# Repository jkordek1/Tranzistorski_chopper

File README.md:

# Tranzistorski_chopper

## O projektu
 Tranzistorski chopper korišten za laboratorijske vježbe na elektrotehničkom odjelu TVZ-a.
 
 ## Značajke
 - Ulazni napon do 24V
 - Potenciometar za promjenu širine impulsa visokog stanja PWM-a
 - Ušice za sonde osciloskopa
 - 3 različite frekvencije PWM-a koje se odabiru pomoću kratkospojnika
 
 ## Slike

## Struktura mape
    .
    ├── ...
    ├── 3d modeli               # 3d modeli komponenata
    ├── Images                  # Slike i grafički elementi dodani na pločicu
    ├── KiCad files             # Glavna mapa KiCAD projekta
    │   ├── Board2Pdf           # Montažna shema
    │   ├── bom                 # ibom pomoćna datoteka za montažu komponenata
    │   ├── Dokumentacija       # Električna shema
    │   ├── gerber              # gerber mapa
    │   └── Slike               # 3D render sklopa
    └── ...

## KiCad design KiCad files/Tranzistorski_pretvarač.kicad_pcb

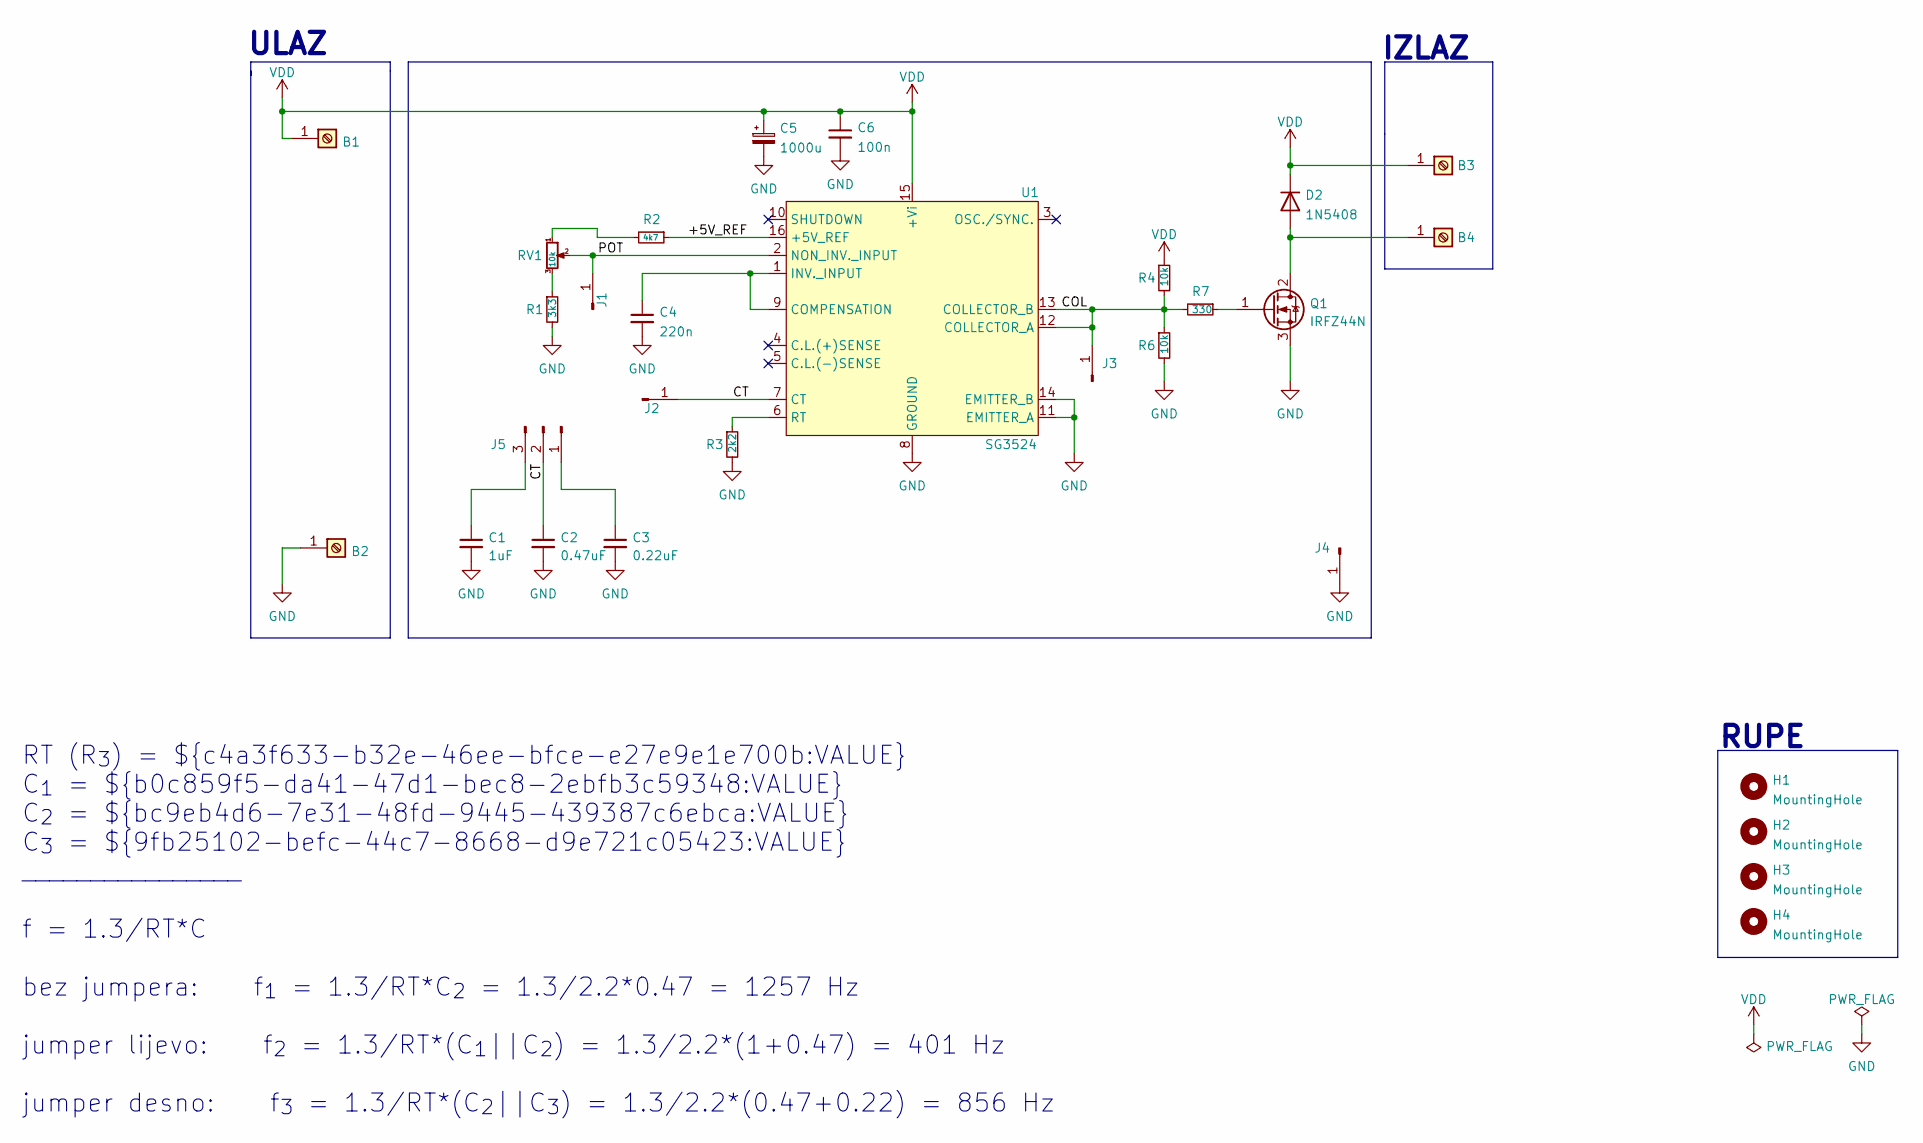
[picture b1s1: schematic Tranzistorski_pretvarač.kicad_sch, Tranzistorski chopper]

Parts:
B1, B3: Screw_Terminal_01x01; DELTRON 4mm banana socket - red
B2, B4: Screw_Terminal_01x01; DELTRON 4mm banana socket - black
C1: 1uF; C_Rect_L7.2mm_W2.5mm_P5.00mm_FKS2_FKP2_MKS2_MKP2
C2: 0.47uF; C_Rect_L7.2mm_W2.5mm_P5.00mm_FKS2_FKP2_MKS2_MKP2
C3: 0.22uF; C_Rect_L7.2mm_W2.5mm_P5.00mm_FKS2_FKP2_MKS2_MKP2
C4: 220n; C_Rect_L7.2mm_W2.5mm_P5.00mm_FKS2_FKP2_MKS2_MKP2
C5: 1000u; CP_Radial_D17.0mm_P7.50mm
C6: 100n; C_Rect_L7.2mm_W2.5mm_P5.00mm_FKS2_FKP2_MKS2_MKP2
D2: 1N5408; D_DO-201AD_P15.24mm_Horizontal
H1, H2, H3, H4: MountingHole; MountingHole_3.2mm_M3
J1, J2, J3, J4: Conn_01x01_Male; oscil
J5: Conn_01x03_Male; PinHeader_1x03_P2.54mm_Vertical
Q1: IRFZ44N; TO-220F-3_Horizontal_TabDown
R1: 3k3; R_Axial_DIN0207_L6.3mm_D2.5mm_P10.16mm_Horizontal
R2: 4k7; R_Axial_DIN0207_L6.3mm_D2.5mm_P10.16mm_Horizontal
R3: 2k2; R_Axial_DIN0207_L6.3mm_D2.5mm_P10.16mm_Horizontal
R4, R6: 10k; R_Axial_DIN0207_L6.3mm_D2.5mm_P10.16mm_Horizontal
R7: 330; R_Axial_DIN0207_L6.3mm_D2.5mm_P10.16mm_Horizontal
RV1: 10k; PTV09A-4225F-B502
U1: SG3524; DIP-16_W7.62mm_Socket_LongPads

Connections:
/+5V_REF: R2.1, U1.16 (+5V_REF)
/COL: J3.1, R4.2, R6.1, R7.2, U1.12 (COLLECTOR_A), U1.13 (COLLECTOR_B)
/CT: C2.1, J2.1, J5.2, U1.7 (CT)
/POT: J1.1, RV1.2, U1.2 (NON_INV._INPUT)
GND: B2.1, C1.2, C2.2, C3.2, C4.2, C5.2, C6.2, J4.1, Q1.3 (S), R1.2, R3.2, R6.2, U1.8 (GROUND), U1.11 (EMITTER_A), U1.14 (EMITTER_B)
unnamed: B4.1, D2.2 (A), Q1.2 (D)
unnamed: C1.1, J5.3
unnamed: C3.1, J5.1
unnamed: C4.1, U1.1 (INV._INPUT), U1.9 (COMPENSATION)
unnamed: Q1.1 (G), R7.1
unnamed: R1.1, RV1.3
unnamed: R2.2, RV1.1
unnamed: R3.1, U1.6 (RT)
VDD: B1.1, B3.1, C5.1, C6.1, D2.1 (K), R4.1, U1.15 (+Vi)

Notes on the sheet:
RUPE
IZLAZ
ULAZ
RT (R_{3}) = ${c4a3f633-b32e-46ee-bfce-e27e9e1e700b:VALUE} C_{1} = ${b0c859f5-da41-47d1-bec8-2ebfb3c59348:VALUE} C_{2} = ${bc9eb4d6-7e31-48fd-9445-439387c6ebca:VALUE} C_{3} = ${9fb25102-befc-44c7-8668-d9e721c05423:VALUE} ________________ f = 1.3/RT*C bez jumpera: f_{1} = 1.3/RT*C_{2} = 1.3/2.2*0.47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

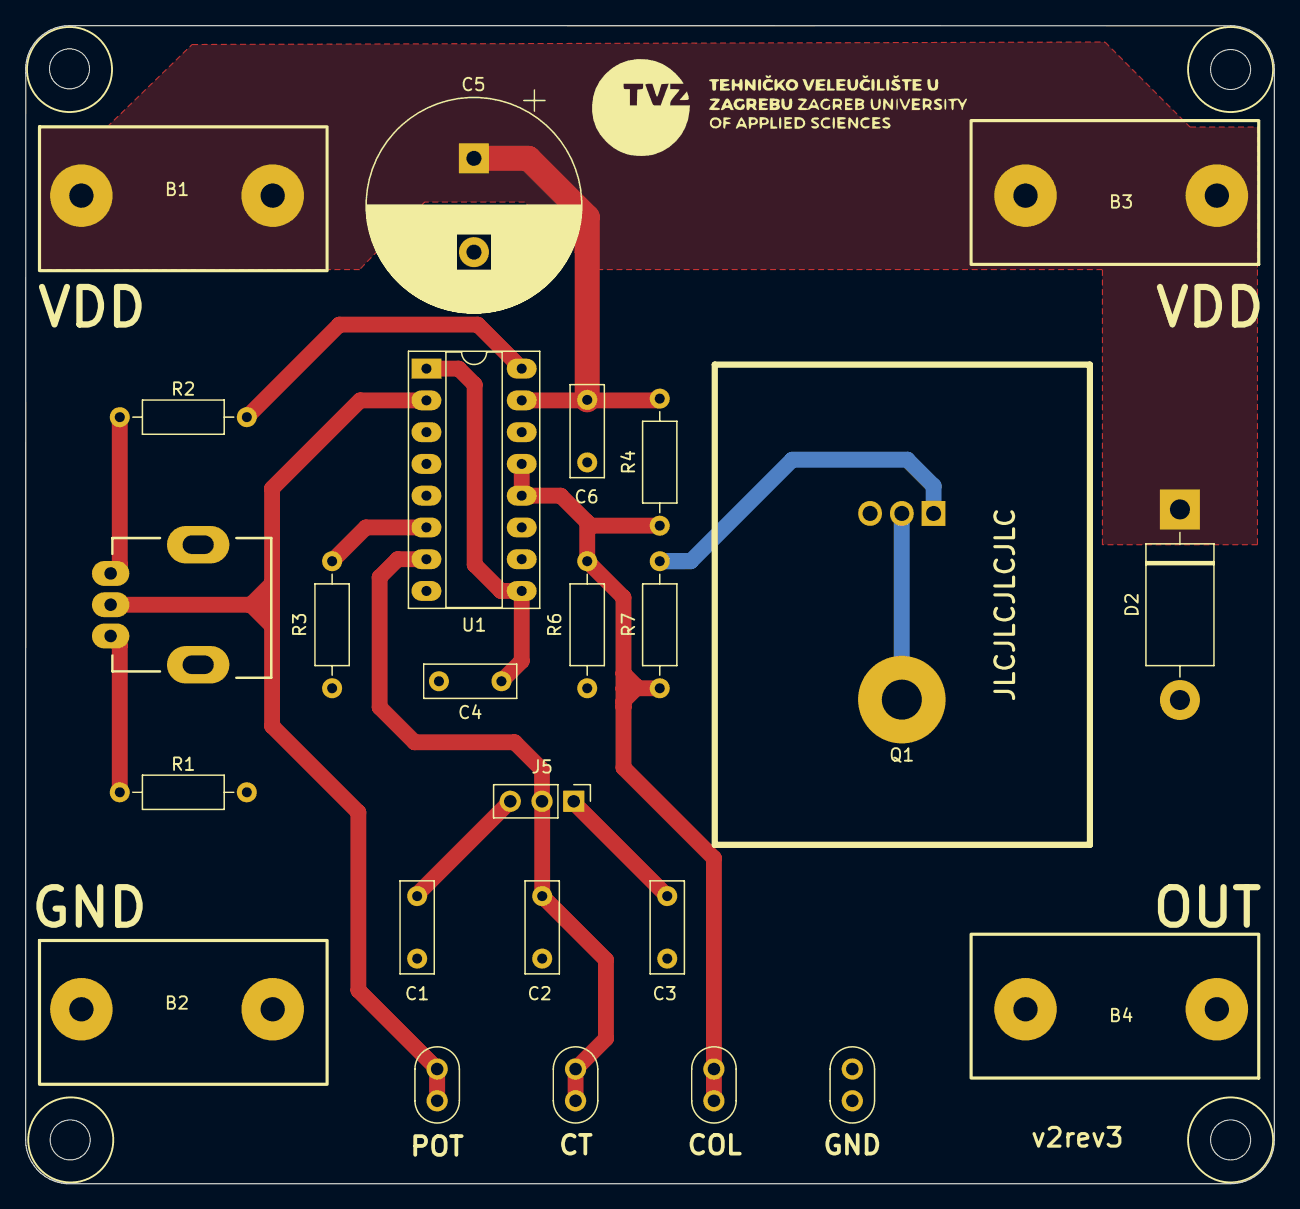
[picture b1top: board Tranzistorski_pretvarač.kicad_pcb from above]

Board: 2 copper layers, 99.9 x 92.6 mm, 29 parts (0 on the bottom side), 14 nets.

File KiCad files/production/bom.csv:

Designator,Footprint,Quantity,Value,LCSC Part #
"B1, B3",DELTRON 4mm banana socket - red,2,Screw_Terminal_01x01,
"B2, B4",DELTRON 4mm banana socket - black,2,Screw_Terminal_01x01,
C1,C_Rect_L7.2mm_W2.5mm_P5.00mm_FKS2_FKP2_MKS2_MKP2,1,1uF,
C2,C_Rect_L7.2mm_W2.5mm_P5.00mm_FKS2_FKP2_MKS2_MKP2,1,0.47uF,
C3,C_Rect_L7.2mm_W2.5mm_P5.00mm_FKS2_FKP2_MKS2_MKP2,1,0.22uF,
C4,C_Rect_L7.2mm_W2.5mm_P5.00mm_FKS2_FKP2_MKS2_MKP2,1,220n,
C5,CP_Radial_D17.0mm_P7.50mm,1,1000u,
C6,C_Rect_L7.2mm_W2.5mm_P5.00mm_FKS2_FKP2_MKS2_MKP2,1,100n,
D2,D_DO-201AD_P15.24mm_Horizontal,1,1N5408,
"H1, H2, H3, H4",MountingHole_3.2mm_M3,4,MountingHole,
"J1, J2, J3, J4",oscil,4,Conn_01x01_Male,
J5,PinHeader_1x03_P2.54mm_Vertical,1,Conn_01x03_Male,
Q1,TO-220F-3_Horizontal_TabDown,1,IRFZ44N,
R1,R_Axial_DIN0207_L6.3mm_D2.5mm_P10.16mm_Horizontal,1,3k3,
R2,R_Axial_DIN0207_L6.3mm_D2.5mm_P10.16mm_Horizontal,1,4k7,
R3,R_Axial_DIN0207_L6.3mm_D2.5mm_P10.16mm_Horizontal,1,2k2,
"R4, R6",R_Axial_DIN0207_L6.3mm_D2.5mm_P10.16mm_Horizontal,2,10k,
R7,R_Axial_DIN0207_L6.3mm_D2.5mm_P10.16mm_Horizontal,1,330,
RV1,PTV09A-4225F-B502,1,10k,
U1,DIP-16_W7.62mm_Socket_LongPads,1,SG3524,

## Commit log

2022-02-10 Initial
2022-02-10 bulk cap
2022-02-12 added probe
2022-02-12 notes
2022-02-13 backup
2022-02-15 gerber
2022-02-22 shema update
2022-03-02 banana
2022-03-03 summary
2022-03-03 layout
2022-03-07 test
2022-03-14 qr code
2022-03-14 remove copper
2022-03-15 final
2022-03-15 thermal
2022-03-16 v2rev2
2022-03-19 6.0.4
2022-04-07 v2rev3
2022-04-11 generate documentation
2022-07-15 dokumentacija
2023-02-14 kicad7
